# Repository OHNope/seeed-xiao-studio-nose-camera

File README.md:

# Rocket Nose Selfie Camera — Minimal Prototype

This prototype treats the Seeed Studio XIAO ESP32-S3 Sense as a module-level part. Its OV3660 camera, microSD, USB power handling, ESP32-S3, and radio circuitry are intentionally not redrawn.

The board is SELFY (自撮り, board 1) of the C-109J stack and follows the team's electrical spec (C-109J 電装仕様書) for its size, mounting holes, inter-board connectors and recommended parts, the same way as `stamp-p4-demo-rec11`.

## Interfaces

| Function | Schematic net / connection |
|---|---|
| Power input | J4 JST S2P-VH (VH, left edge): 1 = `5V_IN`, 2 = GND, from POWER. `5V_IN` → D3 MA10EB045 → `+5V` (XIAO VBUS); `5V_IN` also feeds U2 VDD. XIAO 3V3 output = `+3.3V`; D1/R3 power LED |
| CAN | J3 JST S3B-XH-A (XH, top edge): 1 = CANH, 2 = CANL, 3 = GND, to RT_VIDEO. U3 D4 / GPIO5 = `CAN_TX` → U2 MCP2562-E/SN TXD; U2 RXD → U3 D5 / GPIO6 (`CAN_RX`) |
| Debug trigger | J1 `TRIGGER_IN_EXT` → R1 1 kΩ → `TRIGGER_IN` → U3 D0 / GPIO1; R2 10 kΩ pulldown to GND |
| Debug status | U3 D1 / GPIO2 = `STATUS_OUT` → J1 pin 3; R4 1 kΩ + D2 status LED |

J1 is a 3-pin 2.54 mm debug header (`TRIGGER_IN_EXT`, GND, `STATUS_OUT`). It is not part of the C-109J inter-board wiring, so its position on the board is free.

## Block summary

1. **XIAO ESP32-S3 Sense** — module boundary; camera and microSD remain internal.
2. **Debug trigger / status** — common-ground 3.3 V CMOS active-high input with a series resistor and defined low default; STATUS_OUT exposed on J1.
3. **CAN** — MCP2562-E/SN: VDD from `5V_IN` (C1 100 nF), VIO from `+3.3V` (C2 100 nF), STBY tied to GND (always active). Three-pin CANH/CANL/GND connector J3 and R5 120 Ω termination.
4. **Power indication** — 3V3 power LED.
5. **Power input** — two-pin VH connector J4 from POWER, with Schottky D3 in series.

## Mechanical

- 72 × 72 mm square board.
- Four 4 mm mounting holes H1–H4 in the corners, hole centres 4 mm from each edge (64 mm pitch, C-109J).
- J4 (power) on the left edge, J3 (CAN) on the top edge, both side-entry with the opening at the board edge; U2 next to J3.

## Design notes

- SELFY sits at the end of the CAN bus, so R5 (120 Ω) is fitted. The far end of the bus also needs 120 Ω; with power off, CANH–CANL should measure about 60 Ω across the complete bus.
- J3 carries GND alongside CANH/CANL so the CAN return path stays in the same cable, even though GND is also common through POWER.
- D3 keeps USB 5V from flowing into POWER, and its drop keeps J4 below USB VBUS so J4 does not push current into the USB host when both are connected.
- U2 VDD is on `5V_IN`, ahead of D3: the MCP2562 needs VDD ≥ 4.5 V, and the ~0.35 V Schottky drop would leave too little margin below a 5 V POWER rail. CAN therefore runs only while POWER feeds J4; on USB alone the rest of the stack is unpowered anyway. VIO on `+3.3V` matches the ESP32-S3 I/O levels.
- The debug trigger is assumed to be wired 3.3 V CMOS, active high, with a shared ground.
- Firmware is expected to latch recording on the trigger rising edge and continue recording after the trigger is deasserted.
- D0/D1/D4/D5 assignments are provisional recommendations and must be checked against the exact Seeed XIAO ESP32-S3 Sense hardware revision before flight use.

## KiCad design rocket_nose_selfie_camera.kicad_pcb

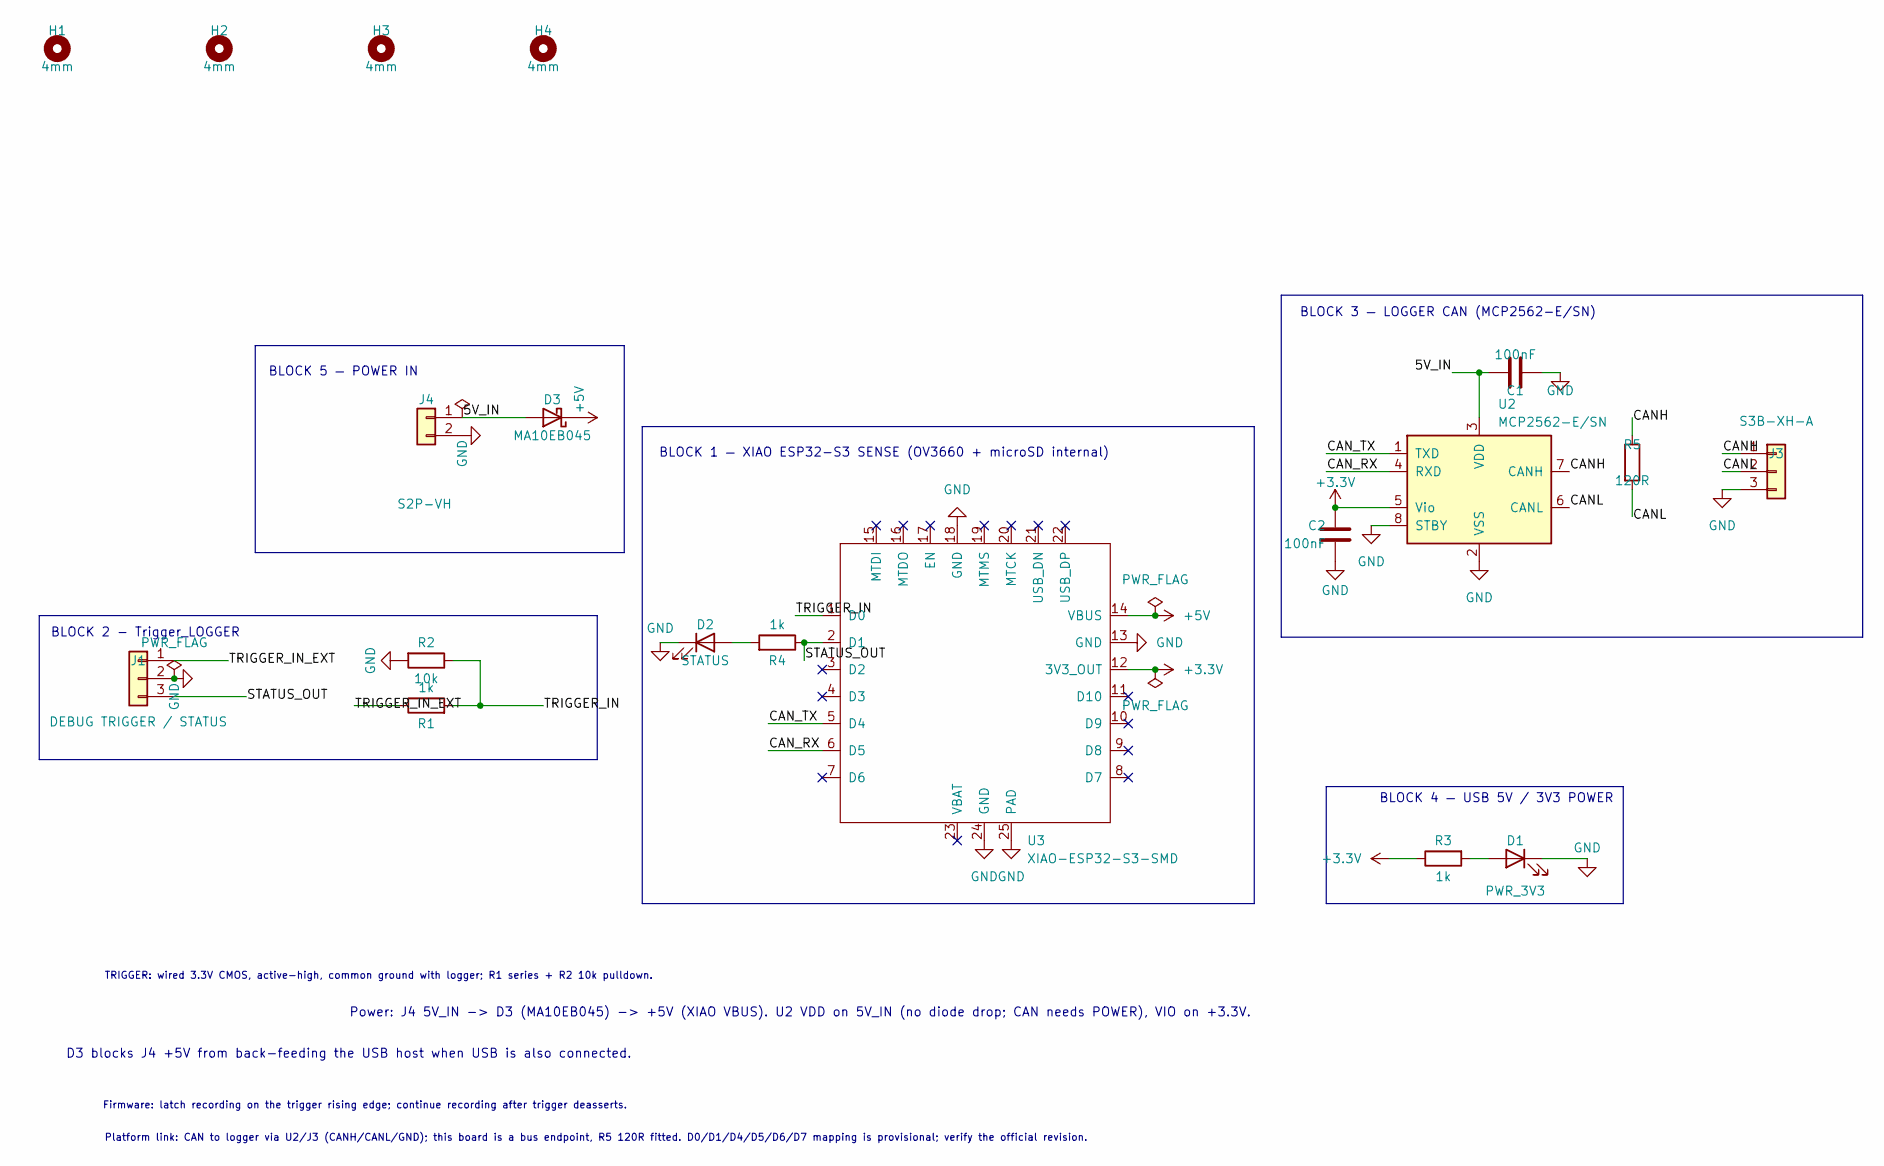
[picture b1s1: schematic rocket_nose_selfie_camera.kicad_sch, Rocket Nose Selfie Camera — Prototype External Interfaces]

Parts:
C1, C2: 100nF; C_0603_1608Metric
D1: PWR_3V3; LED_0603_1608Metric
D2: STATUS; LED_0603_1608Metric
D3: MA10EB045; Vishay_SMPA; MPN MA10EB045
H1, H2, H3, H4: 4mm; MountingHole_4mm
J1: DEBUG TRIGGER / STATUS; PinHeader_1x03_P2.54mm_Vertical
J3: S3B-XH-A; JST_XH_S3B-XH-A_1x03_P2.50mm_Horizontal; MPN S3B-XH-A
J4: S2P-VH; JST_VH_S2P-VH_1x02_P3.96mm_Horizontal; MPN S2P-VH
R1, R3, R4: 1k; R_0603_1608Metric
R2: 10k; R_0603_1608Metric
R5: 120R; R_0603_1608Metric
U2: MCP2562-E/SN; SOIC-8_3.9x4.9mm_P1.27mm; MPN MCP2562-E/SN
U3: XIAO-ESP32-S3-SMD

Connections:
+3.3V: C2.1, R3.1, U2.5 (Vio), U3.12 (3V3_OUT)
+5V: D3.1 (K), U3.14 (VBUS)
/5V_IN: C1.2, D3.2 (A), J4.1, U2.3 (VDD)
/CANH: J3.1, R5.1, U2.7 (CANH)
/CANL: J3.2, R5.2, U2.6 (CANL)
/CAN_RX: U2.4 (RXD), U3.6 (D5)
/CAN_TX: U2.1 (TXD), U3.5 (D4)
/STATUS_OUT: J1.3, R4.1, U3.2 (D1)
/TRIGGER_IN: R1.2, R2.1, U3.1 (D0)
/TRIGGER_IN_EXT: J1.1, R1.1
GND: C1.1, C2.2, D1.1 (K), D2.1 (K), J1.2, J3.3, J4.2, R2.2, U2.2 (VSS), U2.8 (STBY), U3.13 (GND), U3.18 (GND), U3.24 (GND), U3.25 (PAD)
unnamed: D1.2 (A), R3.2
unnamed: D2.2 (A), R4.2

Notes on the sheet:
BLOCK 5 — POWER IN
Firmware: latch recording on the trigger rising edge; continue recording after trigger deasserts.
BLOCK 2 - Trigger_LOGGER
BLOCK 3 — LOGGER CAN (MCP2562-E/SN)
Platform link: CAN to logger via U2/J3 (CANH/CANL/GND); this board is a bus endpoint, R5 120R fitted. D0/D1/D4/D5/D6/D7 mapping is provisional; verify the official revision.
TRIGGER: wired 3.3V CMOS, active-high, common ground with logger; R1 series + R2 10k pulldown.
BLOCK 1 — XIAO ESP32-S3 SENSE (OV3660 + microSD internal)
BLOCK 4 — USB 5V / 3V3 POWER
D3 blocks J4 +5V from back-feeding the USB host when USB is also connected.
Power: J4 5V_IN -> D3 (MA10EB045) -> +5V (XIAO VBUS). U2 VDD on 5V_IN (no diode drop; CAN needs POWER), VIO on +3.3V.

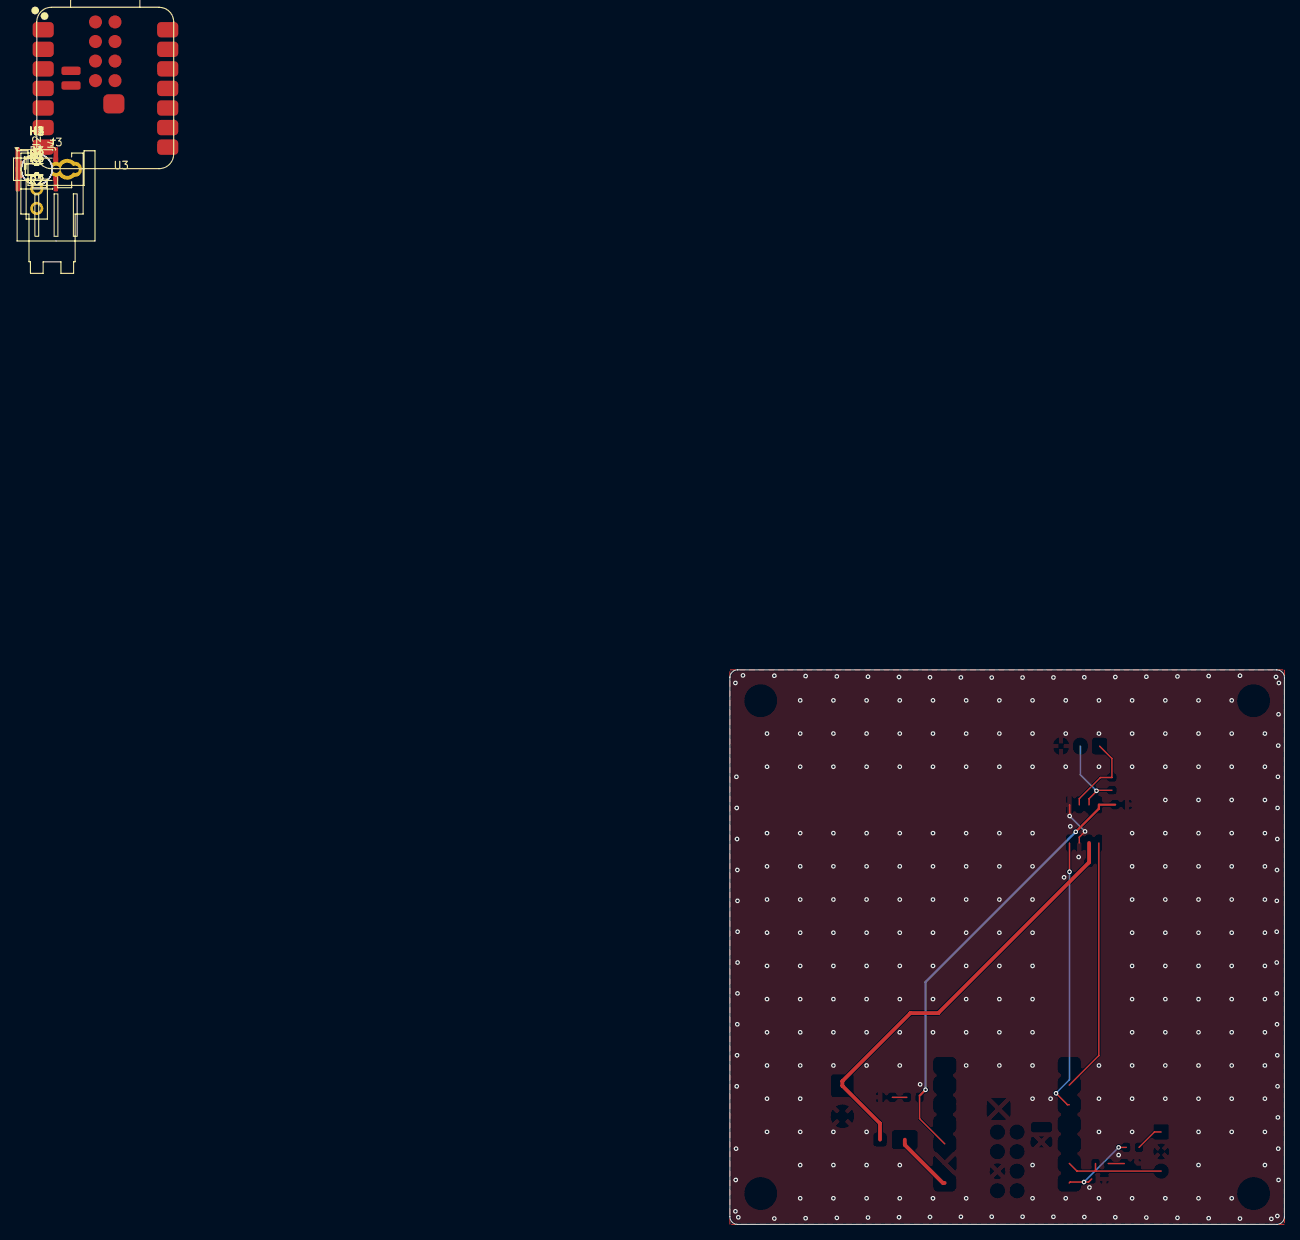
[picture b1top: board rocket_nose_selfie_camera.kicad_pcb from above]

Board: 2 copper layers, 72.0 x 72.0 mm, 19 parts (0 on the bottom side), 13 nets.

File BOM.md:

# BOM — Minimal Prototype

| Ref | Qty | Description | Value / MPN | Notes |
|---|---:|---|---|---|
| U3 | 1 | Seeed Studio XIAO ESP32-S3 Sense module | XIAO-ESP32S3-SENSE | OV3660 and microSD are internal to the module; use the official module footprint |
| U2 | 1 | CAN transceiver | MCP2562-E/SN (SOIC-8) | VDD = 5V_IN, VIO = +3.3V, STBY tied to GND |
| J1 | 1 | 1×03, 2.54 mm header | DEBUG TRIGGER / STATUS | TRIGGER_IN_EXT, GND, STATUS_OUT |
| J3 | 1 | JST XH 3-pin, side entry | S3B-XH-A | 1 CANH, 2 CANL, 3 GND; top edge |
| J4 | 1 | JST VH 2-pin, side entry | S2P-VH | 1 +5V, 2 GND from POWER; left edge |
| D3 | 1 | Schottky diode, DO-221BC | MA10EB045 | Reverse-feed protection, J4 +5V → XIAO VBUS |
| C1 | 1 | Capacitor, 0603 | 100 nF | U2 VDD decoupling (5V_IN) |
| C2 | 1 | Capacitor, 0603 | 100 nF | U2 VIO decoupling (3.3 V) |
| R1 | 1 | Resistor, 0603 | 1 kΩ | Trigger series protection |
| R2 | 1 | Resistor, 0603 | 10 kΩ | Trigger pulldown |
| R3 | 1 | Resistor, 0603 | 1 kΩ | 3V3 power LED current limit |
| R4 | 1 | Resistor, 0603 | 1 kΩ | STATUS_OUT LED current limit |
| R5 | 1 | Resistor, 0603 | 120 Ω | CAN bus termination (SELFY is a bus endpoint) — fitted |
| D1 | 1 | Indicator LED, 0603 | PWR_3V3 | Green or other bring-up indicator colour |
| D2 | 1 | Indicator LED, 0603 | STATUS | Green/yellow or other bring-up indicator colour |
| H1–H4 | 4 | Mounting hole, 4 mm | MountingHole_4mm | Corners, 64 mm pitch |
